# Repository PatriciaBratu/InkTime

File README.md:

README  
  
┌─────────────────────────────────────────────────────────────┐  
│                        POWER SUPPLY                         │  
│                                                             │  
│  Li-Po Battery (3.7V)                                       │  
│       │                                                     │  
│       ▼                                                     │  
│  BQ25180 (Charger IC)  ◄──── USB Type-C (J4)                │  
│       │                                                     │  
│       ▼                                                     │  
│  RT6160A (Buck-Boost)  ──► 3.3V stable output               │  
│       │                                                     │  
│  MAX17048 (Fuel Gauge) ──► I2C ──► nRF52840                 │  
└─────────────────────────────────────────────────────────────┘  
  
┌─────────────────────────────────────────────────────────────┐  
│                    PROCESSING UNIT                          │  
│                                                             │  
│              nRF52840 (ARM Cortex-M4F)                      │  
│        ┌──────────────┴──────────────┐                      │  
│        │                             │                      │  
│      SPI bus                       I2C bus                  │  
│        │                             │                      │  
│  e-Paper Display               ┌─────┴──────┐               │  
│  (1.54" GDEW0154)              │            │               │  
│                            BMA421       DRV2605YZFR         │  
│                           (Accel.)    (Haptic Driver)       │  
└─────────────────────────────────────────────────────────────┘  

Descrierea Funcționalității Hardware  Sistemul InkTime v6 este optimizat pentru autonomie maximă, utilizând componente de ultimă generație.  
## Microcontroller — nRF52840  
Utilizăm SoC-ul **nRF52840** (U1) care integrează un nucleu ARM Cortex-M4F la 64 MHz. Acesta gestionează stiva **Bluetooth Low Energy (BLE)** și coordonează perifericele prin interfețele SPI și I2C.  
  
Sistemul de Alimentare (Power Tree)  
**BQ25180 (IC1):** IC de încărcare liniară cu managementul căii de alimentare (Power Path).  
**MAX17048 (U3):** Fuel Gauge care utilizează algoritmul ModelGauge pentru monitorizarea precisă a stării de încărcare a bateriei via I2C, fără a necesita calibrare manuală.  
**RT6160A (IC9):** Regulator Buck-Boost care menține o ieșire stabilă de 3.3V pe tot parcursul ciclului de descărcare al bateriei (4.2V - 3.0V).  
  
## Afișaj e-Paper (1.54")  
Utilizăm panoul **GDEW0154** conectat prin J1. Consumul este zero între actualizări. Schema include un **E-Paper Drive Circuit** cu inductorul **L5 (5.6uH)** și diode Schottky **MBR0530** (D2, D4, D5) pentru generarea tensiunilor de refresh. Alimentarea este controlată de un MOSFET P-Channel (Q1) pentru a elimina curentul de scurgere în standby.  
  
Senzor de Mișcare și Haptics  
**BMA421 (IC3):** Accelerometru triaxial ultra-low-power utilizat pentru funcția de *tilt-to-wake* și pedometru.  
**DRV2605YZFR (IC2):** Driver haptic specializat care controlează motorul de vibrații, oferind peste 100 de efecte tactile pre-programate via I2C.  
  
## Configurația Pinilor nRF52840  
Maparea pinilor a fost optimizată pentru rutarea pe 4 straturi a PCB-ului:  
+1  

| Semnal   | Pin nRF52 | Direcție      | Descriere                  |
| -------- | --------- | ------------- | -------------------------- |
| EPD_SCK  | P0.28     | Output        | Clock SPI pentru afișaj    |
| EPD_MOSI | P0.29     | Output        | Date imagine către afișaj  |
| EPD_CS   | P0.30     | Output        | Chip Select Display        |
| EPD_DC   | P0.31     | Output        | Data/Command selector      |
| I2C_SDA  | P0.26     | Bidirecțional | Magistrală date senzori    |
| I2C_SCL  | P0.27     | Output        | Magistrală clock senzori   |
| EPD_PWR  | P0.13     | Output        | Control alimentare E-Paper |
| SW_UP    | P1.00     | Input         | Buton Navigare Sus         |
| SW_ENT   | P1.01     | Input         | Buton Selecție             |
| SW_DN    | P1.02     | Input         | Buton Navigare Jos         |

## Calcule Consum Energie (Estimativ)  
* **Deep Sleep (System ON):** ~3.2 μA.  
* **I2C Polling (Senzori):** ~150 μA.  
* **E-Paper Refresh:** ~8 mA (timp de 2 secunde).  
* **Baterie 250 mAh:** Autonomie estimată de **35 zile** (cu 10 refresh-uri/zi și Bluetooth activ).  
## Integrare Mecanică  
Designul a fost validat în Fusion 360 prin analiză de coliziune între baterie și componentele înalte (inductorul L5 și conectorul USB-C). Carcasa WearAwareNewCase oferă o protecție IP67 simbolică.

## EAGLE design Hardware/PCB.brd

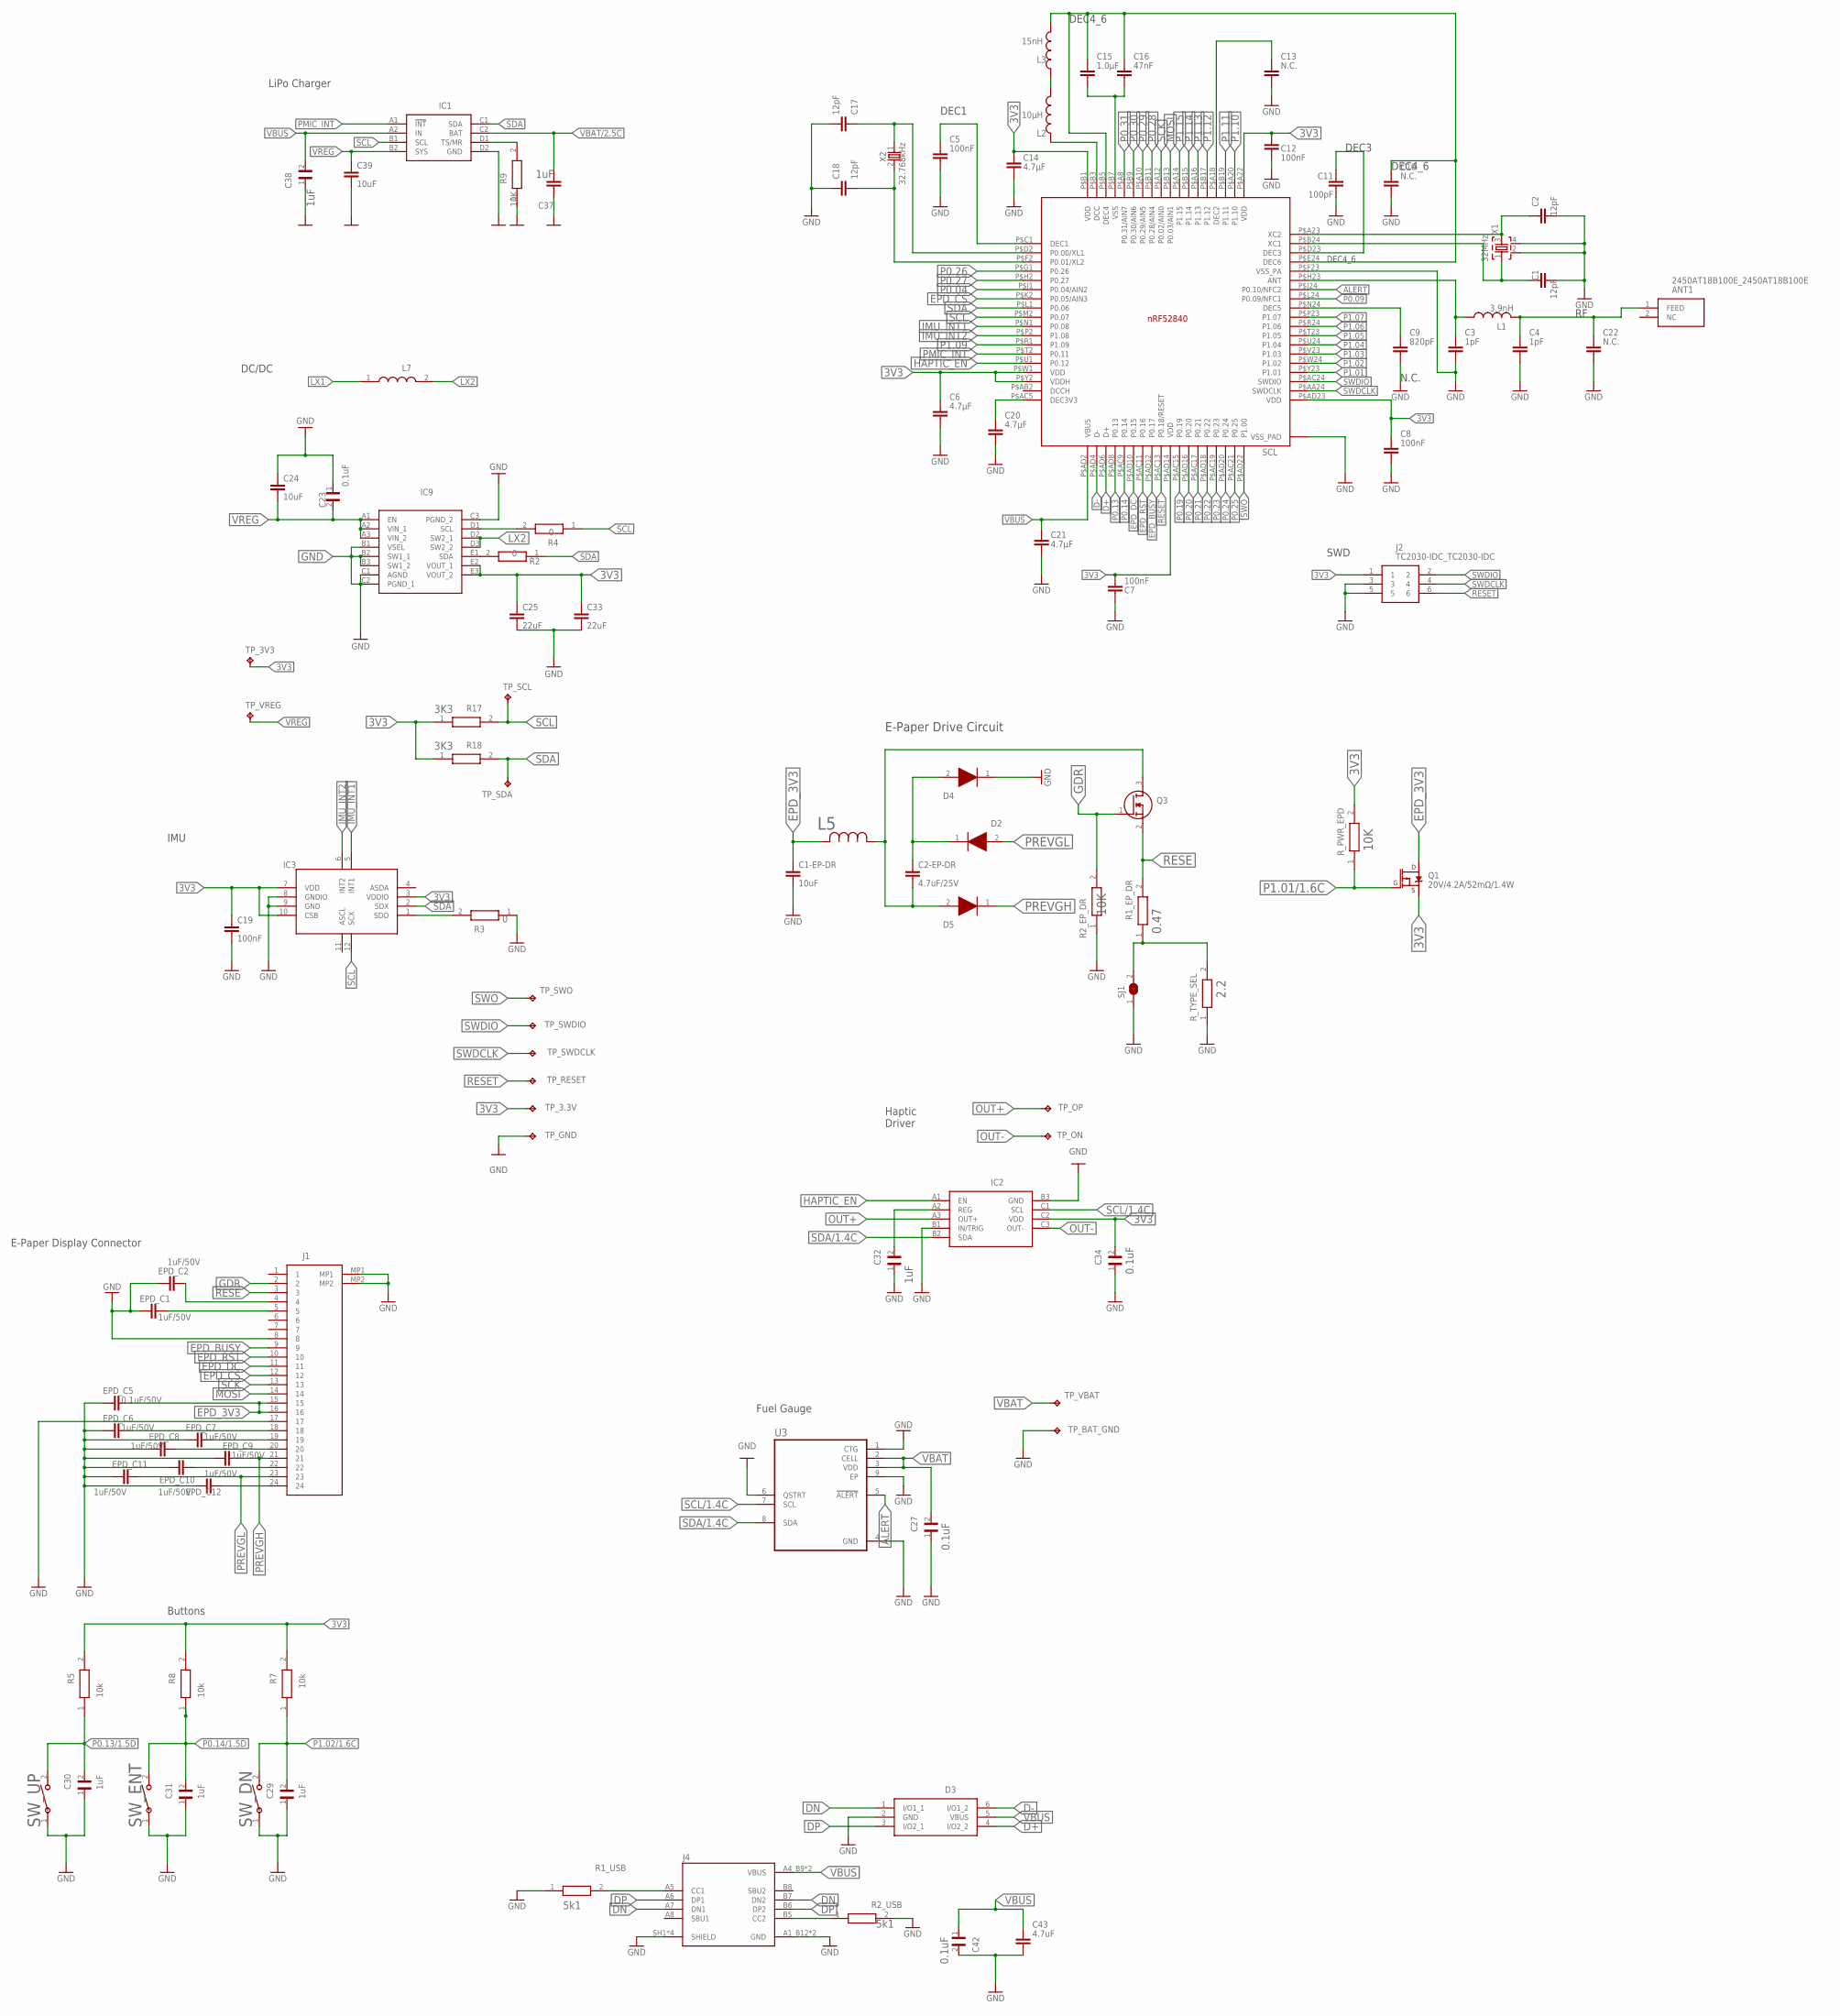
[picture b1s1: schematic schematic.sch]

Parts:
ANT1: 2450AT18B100E_2450AT18B100E; 2450AT18B100E_ANTC3216X140N
C1, C2, C17, C18: 12pF; NORDIC_NRF_3_RESC0201_L
C1-EP-DR, C24, C39: 10uF; NORDIC_NRF_3_RESC0402_L
C2-EP-DR: 4.7uF/25V; NORDIC_NRF_3_RESC0402_L
C3, C4: 1pF; NORDIC_NRF_3_RESC0201_L
C5, C7, C8, C12, C19: 100nF; NORDIC_NRF_3_RESC0201_L
C6, C14, C20, C21: 4.7µF; NORDIC_NRF_3_RESC0402_L
C9: 820pF; NORDIC_NRF_3_RESC0201_L
C10, C13, C22: N.C.; NORDIC_NRF_3_RESC0201_L
C11: 100pF; NORDIC_NRF_3_RESC0201_L
C15: 1.0µF; NORDIC_NRF_3_RESC0402_L
C16: 47nF; NORDIC_NRF_3_RESC0201_L
C23, C27, C29, C30, C31, C32, C34, C38, C42: GRM011R60J152KE01L_2_GRM011R60J152KE01L; GRM011R60J152KE01L_2_CAPC0201X13N
C25, C33: 22uF; NORDIC_NRF_3_RESC0402_L
C37: NORDIC_NRF_3_CAPACITOR_0402_L; NORDIC_NRF_3_RESC0402_L
C43: 4.7uF; NORDIC_NRF_3_RESC0402_L
D2, D4, D5: ESP32_C6_LIBRARY_5_MBR0530; ESP32_C6_LIBRARY_5_SOD3716X135N
D3: ESP32_C6_LIBRARY_3_USBLC6-2SC6Y; ESP32_C6_LIBRARY_3_SOT95P280X145-6N
EPD_C1, EPD_C2, EPD_C6, EPD_C7, EPD_C8, EPD_C9, EPD_C10, EPD_C11, EPD_C12: 1uF/50V; NORDIC_NRF_3_RESC0402_L
EPD_C5: 0.1uF/50V; NORDIC_NRF_3_RESC0402_L
IC1: BQ25180YBGR_BQ25180YBGR; BQ25180YBGR_BGA8C40P2X4_100X155X50
IC2: DRV2605YZFR_DRV2605YZFR; DRV2605YZFR_BGA9C50P3X3_144X144X62
IC3: BMA423_BMA423
IC9: RT6160AWSC_RT6160AWSC; RT6160AWSC_BGA15C40P3X5_140X230X60
J1: 503480-2400_503480-2400; 503480-2400_5034802400
J2: TC2030-IDC_TC2030-IDC; TC2030-IDC_TC2030IDC
J4: KH-TYPE-C-16P_KH-TYPE-C-16P; KH-TYPE-C-16P_KINGHELM_KH-TYPE-C-16P
L1: 3.9nH; NORDIC_NRF_2_RESC0201_L
L2: 10µH; NORDIC_NRF_2_RESC0201_L
L3: 15nH; NORDIC_NRF_2_RESC0201_L
L5: 10uH; ESP32_C6_LIBRARY_2_IND_4828-WE-TPC_WRE
L7: MLP2016SR47MT0S1_FTC252012SR47MBCA; MLP2016SR47MT0S1_INDC2016X100N
Q1: 20V/4.2A/52mΩ/1.4W; ESP32_C6_LIBRARY_4_ESP32_C6_LIBRARY_4_ESP32_C6_LIBRARY_4_ES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
Q3: ESP32_C6_LIBRARY_6_SI1308EDL-T1-GE3; ESP32_C6_LIBRARY_6_SOT65P210X110-3N
R1_EP_DR, R1_USB, R2_EP_DR, R2_USB, R3: ERA-1AEB3401C_CPF0201D7K68C1; ERA-1AEB3401C_0201
R2, R4, R5, R7, R8, R17, R18: CPF0201D7K68C1_CPF0201D7K68C1; CPF0201D7K68C1_0201
R9: 10k; CPF0201D7K68C1_0201
R_PWR_EPD: ERA-1AEB3401C_CPF0201D7K68C1; ERA-1AEB3401C_0201
R_TYPE_SEL: ERA-1AEB3401C_CPF0201D7K68C1; ERA-1AEB3401C_0201
SCL: NORDIC_NRF_4_NRF52840_QF; NORDIC_NRF_4_AQFN50P700X700X85_HS-74N
SJ1: ESP32_C6_LIBRARY_7_JUMPER_SJ
SW_DN: 2025-10-22_07-23-44_LIBRARY_EVP-AKE31ASW_EVP-AKE3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; 2025-10-22_07-23-44_LIBRARY_SW_EVP-AKE31A_PAN
SW_ENT: 2025-10-22_07-23-44_LIBRARY_EVP-AKE31ASW_EVP-AKE3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; 2025-10-22_07-23-44_LIBRARY_SW_EVP-AKE31A_PAN
SW_UP: 2025-10-22_07-23-44_LIBRARY_EVP-AKE31ASW_EVP-AKE3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; 2025-10-22_07-23-44_LIBRARY_SW_EVP-AKE31A_PAN
TP_3.3V, TP_3V3: HECTOR_WATCH_1_TPTP20R; HECTOR_WATCH_1_TP20R
TP_BAT_GND: HECTOR_WATCH_1_TPTP20R; HECTOR_WATCH_1_TP20R
TP_GND: HECTOR_WATCH_1_TPTP20R; HECTOR_WATCH_1_TP20R
TP_ON: HECTOR_WATCH_1_TPTP20R; HECTOR_WATCH_1_TP20R
TP_OP: HECTOR_WATCH_1_TPTP20R; HECTOR_WATCH_1_TP20R
TP_RESET: HECTOR_WATCH_1_TPTP20R; HECTOR_WATCH_1_TP20R
TP_SCL: HECTOR_WATCH_1_TPTP20R; HECTOR_WATCH_1_TP20R
TP_SDA: HECTOR_WATCH_1_TPTP20R; HECTOR_WATCH_1_TP20R
TP_SWDCLK: HECTOR_WATCH_1_TPTP20R; HECTOR_WATCH_1_TP20R
TP_SWDIO: HECTOR_WATCH_1_TPTP20R; HECTOR_WATCH_1_TP20R
TP_SWO: HECTOR_WATCH_1_TPTP20R; HECTOR_WATCH_1_TP20R
TP_VBAT: HECTOR_WATCH_1_TPTP20R; HECTOR_WATCH_1_TP20R
TP_VREG: HECTOR_WATCH_1_TPTP20R; HECTOR_WATCH_1_TP20R
U3: ESP32_C6_LIBRARY_MAX17048G+T10; ESP32_C6_LIBRARY_SON50P200X200X80-9N
X1: 32MHz; NORDIC_NRF_BT-XTAL_2016_N
X2: 32.768kHz; NORDIC_NRF_1_XTAL_3215_N

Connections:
3V3: C6.1, C7.1, C8.1, C12.1, C14.1, C19.1, C25.1, C33.1, C34.2, IC2.C2 (VDD), IC3.3 (VDDIO), IC3.7 (VDD), IC3.10 (CSB), IC9.E2 (VOUT_1), IC9.E3 (VOUT_2), J2.1, Q1.2 (S), R5.2, R7.2, R8.2, R17.1, R18.1, R_PWR_EPD.2, SCL.P$A22 (VDD), SCL.P$AD14 (VDD), SCL.P$AD23 (VDD), SCL.P$B1 (VDD), SCL.P$W1 (VDD), SCL.P$Y2 (VDDH), TP_3.3V.TP, TP_3V3.TP
ALERT: SCL.P$J24 (P0.10/NFC2), U3.5 (!ALERT)
D+: D3.4 (I/O2_2), SCL.P$AD6 (D+)
D-: D3.6 (I/O1_2), SCL.P$AD4 (D-)
DN: D3.1 (I/O1_1), J4.A7 (DN1), J4.B7 (DN2)
DP: D3.3 (I/O2_1), J4.A6 (DP1), J4.B6 (DP2)
EPD_3V3: C1-EP-DR.1, EPD_C5.2, J1.15, J1.16, L5.2, Q1.3 (D)
EPD_BUSY: J1.9, SCL.P$AD12 (P0.17)
EPD_CS: J1.12, SCL.P$K2 (P0.05/AIN3)
EPD_DC: J1.11, SCL.P$AD10 (P0.15)
EPD_RST: J1.10, SCL.P$AC11 (P0.16)
GDR: J1.2, Q3.1 (G), R2_EP_DR.2
GND: C1.2, C1-EP-DR.2, C2.2, C3.2, C4.2, C5.2, C6.2, C7.2, C8.2, C9.2, C10.2, C11.2, C12.2, C13.2, C14.2, C17.1, C18.1, C19.2, C20.2, C21.2, C22.2, C23.1, C24.1, C25.2, C27.1, C29.1, C30.1, C31.1, C32.1, C33.2, C34.1, C37.1, C38.1, C39.2, C42.2, C43.2, D3.2 (GND), D4.1 (K), EPD_C1.1, EPD_C2.1, EPD_C5.1, EPD_C6.1, EPD_C7.1, EPD_C8.1, EPD_C9.1, EPD_C10.1, EPD_C11.1, EPD_C12.1, IC1.D2 (GND), IC2.B1 (IN/TRIG), IC2.B3 (GND), IC3.8 (GNDIO), IC3.9 (GND), IC9.B1 (VSEL), IC9.B2 (SW1_1), IC9.B3 (SW1_2), IC9.C1 (AGND), IC9.C2 (PGND_1), IC9.C3 (PGND_2), J1.8, J1.17, J1.MP1, J1.MP2, J2.3, J2.5, J4.A1_B12 (GND), J4.A12_B1 (GND), J4.SH1 (SHIELD), J4.SH2 (SHIELD), J4.SH3 (SHIELD), J4.SH4 (SHIELD), R1_USB.1, R2_EP_DR.1, R2_USB.2, R3.1, R9.1, R_TYPE_SEL.1, SCL.P$74 (VSS_PAD), SCL.P$75 (VSS_PAD), SCL.P$76 (VSS_PAD), SCL.P$77 (VSS_PAD), SCL.P$78 (VSS_PAD), SCL.P$79 (VSS_PAD), SCL.P$80 (VSS_PAD), SCL.P$81 (VSS_PAD), SCL.P$82 (VSS_PAD), SCL.P$83 (VSS_PAD), SCL.P$84 (VSS_PAD), SCL.P$85 (VSS_PAD), SCL.P$86 (VSS_PAD), SCL.P$87 (VSS_PAD), SCL.P$88 (VSS_PAD), SCL.P$89 (VSS_PAD), SCL.P$90 (VSS_PAD), SCL.P$F23 (VSS_PA), SJ1.1, SW_DN.1, SW_ENT.1, SW_UP.1, TP_BAT_GND.TP, TP_GND.TP, U3.1 (CTG), U3.4 (GND), U3.6 (QSTRT), U3.9 (EP), X1.2, X1.4
HAPTIC_EN: IC2.A1 (EN), SCL.P$U1 (P0.12)
IMU_INT1: IC3.5 (INT1), SCL.P$N1 (P0.08)
IMU_INT2: IC3.6 (INT2), SCL.P$P2 (P1.08)
LX1: L7.1
LX2: IC9.D2 (SW2_1), IC9.D3 (SW2_2), L7.2
MOSI: J1.14, SCL.P$B13 (P0.03/AIN1)
unnamed: IC9.D1 (SCL), R4.2
unnamed: C20.1, SCL.P$AC5 (DEC3V3)
unnamed: IC1.D1 (TS/MR), R9.2
unnamed: L2.2, L3.1
unnamed: C11.1, SCL.P$D23 (DEC3)
unnamed: IC9.E1 (SDA), R2.2
unnamed: L2.1, SCL.P$B3 (DCC)
unnamed: C10.1, C15.1, C16.1, L3.2, SCL.P$B5 (DEC4), SCL.P$E24 (DEC6)
unnamed: IC3.1 (SDO), R3.2
unnamed: C13.1, SCL.P$A18 (DEC2)
unnamed: EPD_C12.2, J1.24
unnamed: C2.1, SCL.P$A23 (XC2), X1.3
unnamed: C1.1, SCL.P$B24 (XC1), X1.1
unnamed: C9.1, SCL.P$N24 (DEC5)
unnamed: C3.1, L1.1, SCL.P$H23 (ANT)
unnamed: ANT1.1 (FEED), C4.1, C22.1, L1.2
unnamed: C15.2, C16.2, SCL.P$B7 (VSS)
unnamed: C18.2, SCL.P$F2 (P0.01/XL2), X2.2
unnamed: C17.2, SCL.P$D2 (P0.00/XL1), X2.1
unnamed: C5.1, SCL.P$C1 (DEC1)
unnamed: C2-EP-DR.1, D2.1 (K), D4.2 (A)
unnamed: EPD_C1.2, J1.5
unnamed: EPD_C2.2, J1.4
unnamed: J4.B5 (CC2), R2_USB.1
unnamed: R1_EP_DR.1, R_TYPE_SEL.2, SJ1.2
unnamed: C32.2, IC2.A2 (REG)
unnamed: J4.A5 (CC1), R1_USB.2
unnamed: EPD_C6.2, J1.18
unnamed: EPD_C7.2, J1.19
unnamed: EPD_C8.2, J1.20
unnamed: EPD_C10.2, J1.22
NGD: C2-EP-DR.2, D5.2 (A), L5.1, Q3.3 (D)
OUT+: IC2.A3 (OUT+), TP_OP.TP
OUT-: IC2.C3 (OUT-), TP_ON.TP
P0.04: SCL.P$J1 (P0.04/AIN2)
P0.09: SCL.P$L24 (P0.09/NFC1)
P0.13: SCL.P$AD8 (P0.13)
P0.13/1.5D: C30.2, R5.1, SW_UP.2
P0.14: SCL.P$AC9 (P0.14)
P0.14/1.5D: C31.2, R8.1, SW_ENT.2
P0.19: SCL.P$AC15 (P0.19)
P0.20: SCL.P$AD16 (P0.20)
P0.21: SCL.P$AC17 (P0.21)
P0.22: SCL.P$AD18 (P0.22)
P0.23: SCL.P$AC19 (P0.23)
P0.24: SCL.P$AD20 (P0.24)
P0.25: SCL.P$AC21 (P0.25)
P0.26: SCL.P$G1 (P0.26)
P0.27: SCL.P$H2 (P0.27)
P0.28: SCL.P$B11 (P0.28/AIN4)
P0.29: SCL.P$A10 (P0.29/AIN5)
P0.30: SCL.P$B9 (P0.30/AIN6)
P0.31: SCL.P$A8 (P0.31/AIN7)
P1.01: SCL.P$Y23 (P1.01)
P1.01/1.6C: Q1.1 (G), R_PWR_EPD.1
P1.02: SCL.P$W24 (P1.02)
P1.02/1.6C: C29.2, R7.1, SW_DN.2
P1.03: SCL.P$V23 (P1.03)
P1.04: SCL.P$U24 (P1.04)
P1.05: SCL.P$T23 (P1.05)
P1.06: SCL.P$R24 (P1.06)
P1.07: SCL.P$P23 (P1.07)
P1.09: SCL.P$R1 (P1.09)
P1.10: SCL.P$A20 (P1.10)
P1.11: SCL.P$B19 (P1.11)
P1.12: SCL.P$B17 (P1.12)
P1.13: SCL.P$A16 (P1.13)
P1.14: SCL.P$B15 (P1.14)
P1.15: SCL.P$A14 (P1.15)
PMIC_INT: IC1.A1 (!INT), SCL.P$T2 (P0.11)
PREVGH: D5.1 (K), EPD_C9.2, J1.21
PREVGL: D2.2 (A), EPD_C11.2, J1.23
RESE: J1.3, Q3.2 (S), R1_EP_DR.2
RESET: J2.6, SCL.P$AC13 (P0.18/RESET), TP_RESET.TP
SCK: J1.13, SCL.P$A12 (P0.02/AIN0)
SCL: IC1.B1 (SCL), IC3.12 (SCX), R4.1, R17.2, SCL.P$M2 (P0.07), TP_SCL.TP
SCL/1.4C: IC2.C1 (SCL), U3.7 (SCL)
SDA: IC1.C1 (SDA), IC3.2 (SDX), R2.1, R18.2, SCL.P$L1 (P0.06), TP_SDA.TP
SDA/1.4C: IC2.B2 (SDA), U3.8 (SDA)
SWDCLK: J2.4, SCL.P$AA24 (SWDCLK), TP_SWDCLK.TP
SWDIO: J2.2, SCL.P$AC24 (SWDIO), TP_SWDIO.TP
SWO: SCL.P$AD22 (P1.00), TP_SWO.TP
VBAT: C27.2, TP_VBAT.TP, U3.2 (CELL), U3.3 (VDD)
VBAT/2.5C: C37.2, IC1.C2 (BAT)
VBUS: C21.1, C38.2, C42.1, C43.1, D3.5 (VBUS), IC1.A2 (IN), J4.A4_B9 (VBUS), J4.A9_B4 (VBUS), SCL.P$AD2 (VBUS)
VREG: C23.2, C24.2, C39.1, IC1.B2 (SYS), IC9.A1 (EN), IC9.A2 (VIN_1), IC9.A3 (VIN_2), TP_VREG.TP

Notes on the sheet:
LiPo Charger
DC/DC
IMU
DEC1
DEC4_6
DEC3
N.C.
DEC4_6
E-Paper Drive Circuit
SWD
E-Paper Display Connector
Haptic Driver
Fuel Gauge
Buttons

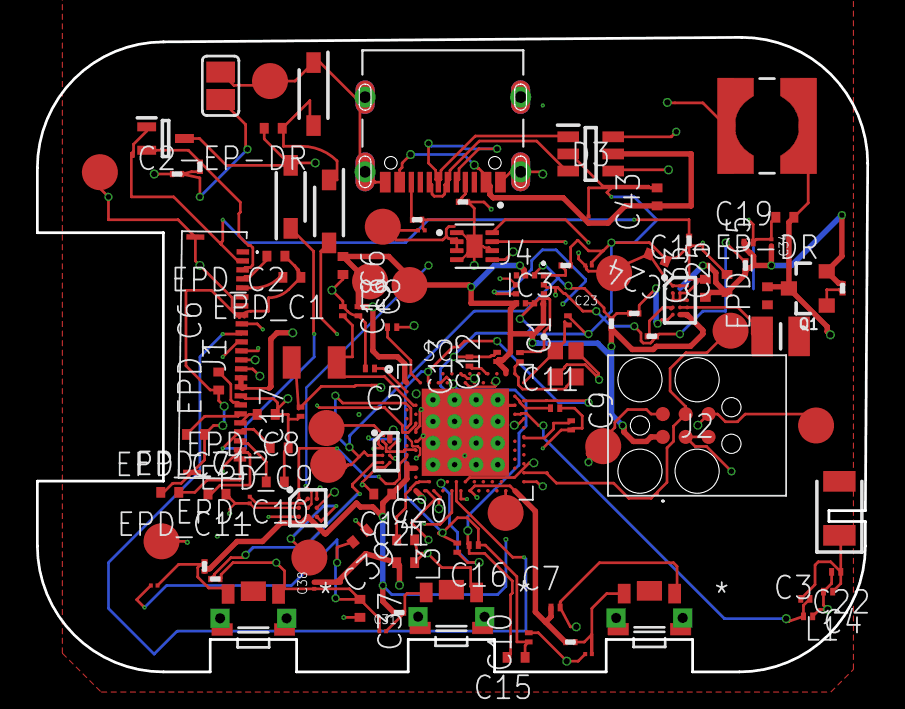
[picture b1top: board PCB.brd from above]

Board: 4 copper layers, 46.1 x 35.3 mm, 105 parts (0 on the bottom side), 73 nets.

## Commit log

2026-04-20 Inlocuit toate fisierele cu versiunea noua
2026-04-20 Add GNU GPL v3 license
    Added the GNU General Public License version 3 to the project.

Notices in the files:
parts and their libraries:
COPYRIGHT: Copyright (C) 2024 Ultra Librarian. All rights reserved.
COPYRIGHT: Copyright (C) 2025 Ultra Librarian. All rights reserved.
